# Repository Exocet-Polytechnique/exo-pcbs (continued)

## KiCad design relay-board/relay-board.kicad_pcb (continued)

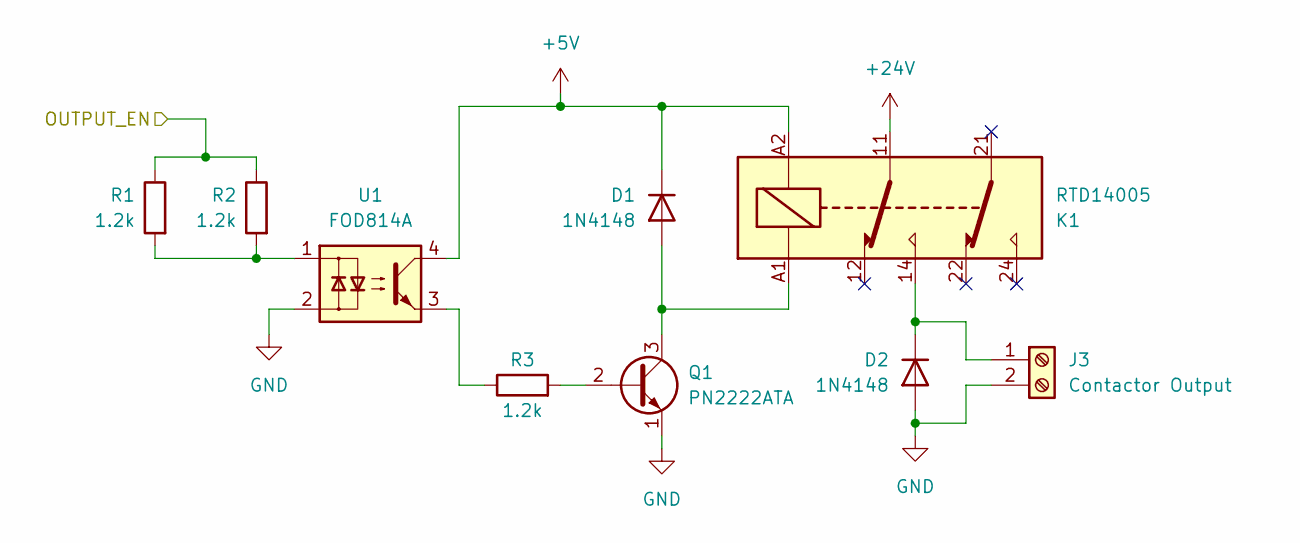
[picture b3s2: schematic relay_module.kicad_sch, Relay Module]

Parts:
D1, D2: 1N4148; D_DO-35_SOD27_P7.62mm_Horizontal
J3: Contactor Output; Wurth_Term_Blk_2pos_Side_Entry_5mm; MPN 691137710002
K1: RTD14005; Relay_DPDT_Schrack-RT2-FormC_RM5mm
Q1: PN2222ATA; TO-92_Inline
R1, R2, R3: 1.2k; R_Axial_DIN0207_L6.3mm_D2.5mm_P10.16mm_Horizontal
U1: FOD814A; DIP-4_W7.62mm

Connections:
+5V: D1.1 (K), K1.A2, U1.4; also elsewhere on the board
+24V: K1.11; also elsewhere on the board
/BOP_SWITCH: R1.1, R2.1; also elsewhere on the board
GND: D2.2 (A), J3.2, Q1.1 (E), U1.2; also elsewhere on the board
unnamed: D1.2 (A), K1.A1, Q1.3 (C)
unnamed: D2.1 (K), J3.1, K1.14
unnamed: Q1.2 (B), R3.2
unnamed: R1.2, R2.2, U1.1
unnamed: R3.1, U1.3

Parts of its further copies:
D3, D4, D5, D6, D7, D8, D9, D10, D11, D12, D13, D14, D15, D16: 1N4148; D_DO-35_SOD27_P7.62mm_Horizontal
J4, J5, J6, J7, J8, J9, J10: Contactor Output; Wurth_Term_Blk_2pos_Side_Entry_5mm; MPN 691137710002
K2, K3, K4, K5, K6, K7, K8: RTD14005; Relay_DPDT_Schrack-RT2-FormC_RM5mm
Q2, Q3, Q4, Q5, Q6, Q7, Q8: PN2222ATA; TO-92_Inline
R4, R5, R6, R7, R8, R9, R10, R11, R12, R13, R14, R15, R16, R17, R18, R19, R20, R21, R22, R23, R24: 1.2k; R_Axial_DIN0207_L6.3mm_D2.5mm_P10.16mm_Horizontal
U2, U3, U4, U5, U6, U7, U8: FOD814A; DIP-4_W7.62mm

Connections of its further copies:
+5V: D3.1 (K), D5.1 (K), D7.1 (K), D9.1 (K), D11.1 (K), D13.1 (K), D15.1 (K), K2.A2, K3.A2, K4.A2, K5.A2, K6.A2, K7.A2, K8.A2, U2.4, U3.4, U4.4, U5.4, U6.4, U7.4, U8.4; also elsewhere on the board
+24V: K2.11, K3.11, K4.11, K5.11, K6.11, K7.11, K8.11; also elsewhere on the board
/AUXILIARY_BATTERY_SWITCH: R22.1, R23.1; also elsewhere on the board
/BRAKING_RESISTOR: R19.1, R20.1; also elsewhere on the board
/MOTOR_PRECHARGE_STAGE_1: R13.1, R14.1; also elsewhere on the board
/MOTOR_PRECHARGE_STAGE_2: R16.1, R17.1; also elsewhere on the board
/MPPT_PRECHARGE_STAGE_1: R7.1, R8.1; also elsewhere on the board
/MPPT_PRECHARGE_STAGE_2: R10.1, R11.1; also elsewhere on the board
/STORAGE_BATTERY_SWITCH: R4.1, R5.1; also elsewhere on the board
GND: D4.2 (A), D6.2 (A), D8.2 (A), D10.2 (A), D12.2 (A), D14.2 (A), D16.2 (A), J4.2, J5.2, J6.2, J7.2, J8.2, J9.2, J10.2, Q2.1 (E), Q3.1 (E), Q4.1 (E), Q5.1 (E), Q6.1 (E), Q7.1 (E), Q8.1 (E), U2.2, U3.2, U4.2, U5.2, U6.2, U7.2, U8.2; also elsewhere on the board
unnamed: D3.2 (A), K2.A1, Q2.3 (C)
unnamed: D4.1 (K), J4.1, K2.14
unnamed: D5.2 (A), K3.A1, Q3.3 (C)
unnamed: D6.1 (K), J5.1, K3.14
unnamed: D7.2 (A), K4.A1, Q4.3 (C)
unnamed: D8.1 (K), J6.1, K4.14
unnamed: D9.2 (A), K5.A1, Q5.3 (C)
unnamed: D10.1 (K), J7.1, K5.14
unnamed: D11.2 (A), K6.A1, Q6.3 (C)
unnamed: D12.1 (K), J8.1, K6.14
unnamed: D13.2 (A), K7.A1, Q7.3 (C)
unnamed: D14.1 (K), J9.1, K7.14
unnamed: D15.2 (A), K8.A1, Q8.3 (C)
unnamed: D16.1 (K), J10.1, K8.14
unnamed: Q2.2 (B), R6.2
unnamed: Q3.2 (B), R9.2
unnamed: Q4.2 (B), R12.2
unnamed: Q5.2 (B), R15.2
unnamed: Q6.2 (B), R18.2
unnamed: Q7.2 (B), R21.2
unnamed: Q8.2 (B), R24.2
unnamed: R4.2, R5.2, U2.1
unnamed: R6.1, U2.3
unnamed: R7.2, R8.2, U3.1
unnamed: R9.1, U3.3
unnamed: R10.2, R11.2, U4.1
unnamed: R12.1, U4.3
unnamed: R13.2, R14.2, U5.1
unnamed: R15.1, U5.3
unnamed: R16.2, R17.2, U6.1
unnamed: R18.1, U6.3
unnamed: R19.2, R20.2, U7.1
unnamed: R21.1, U7.3
unnamed: R22.2, R23.2, U8.1
unnamed: R24.1, U8.3

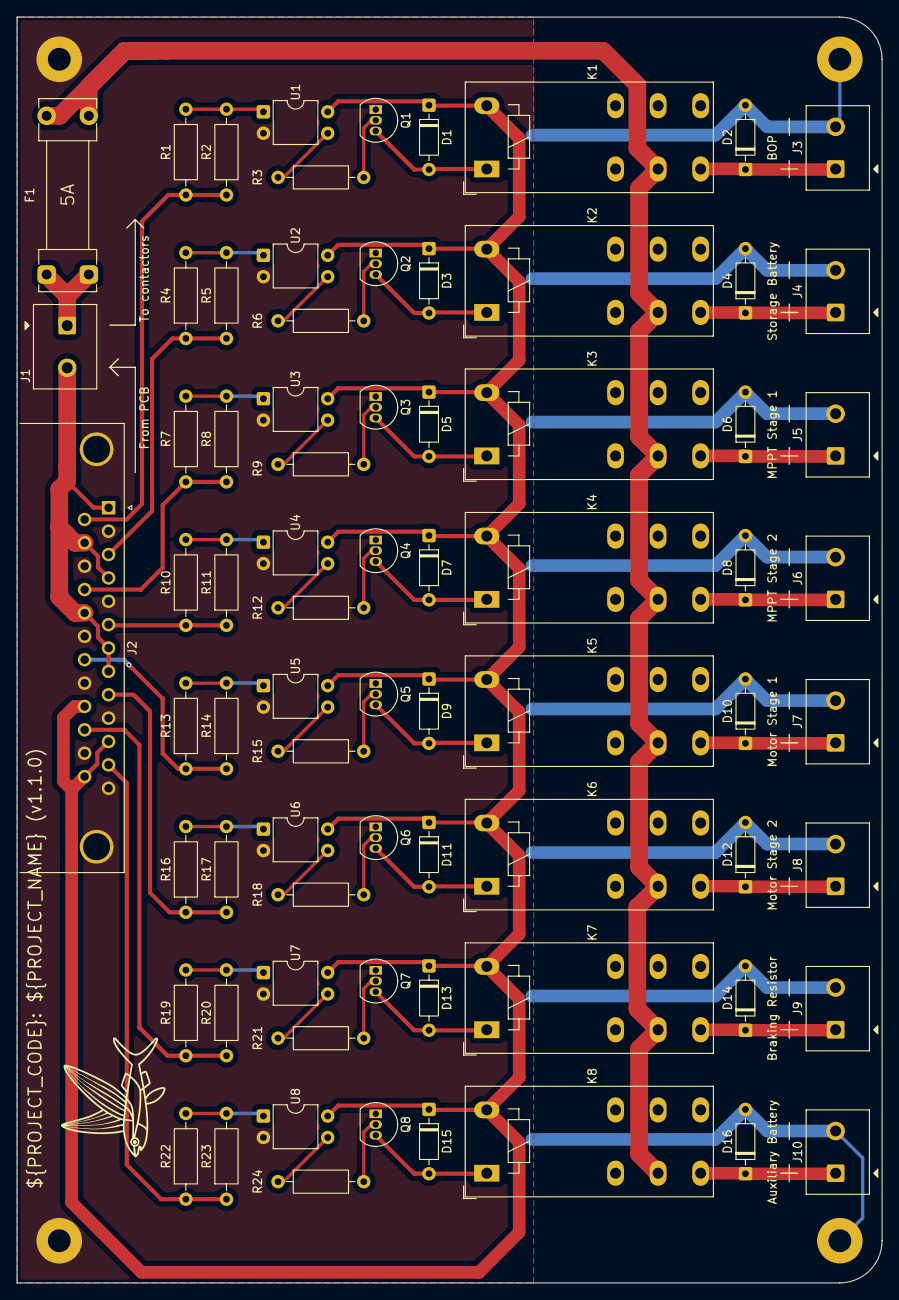
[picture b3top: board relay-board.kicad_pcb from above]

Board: 2 copper layers, 102.5 x 150.0 mm, 79 parts (0 on the bottom side), 53 nets.

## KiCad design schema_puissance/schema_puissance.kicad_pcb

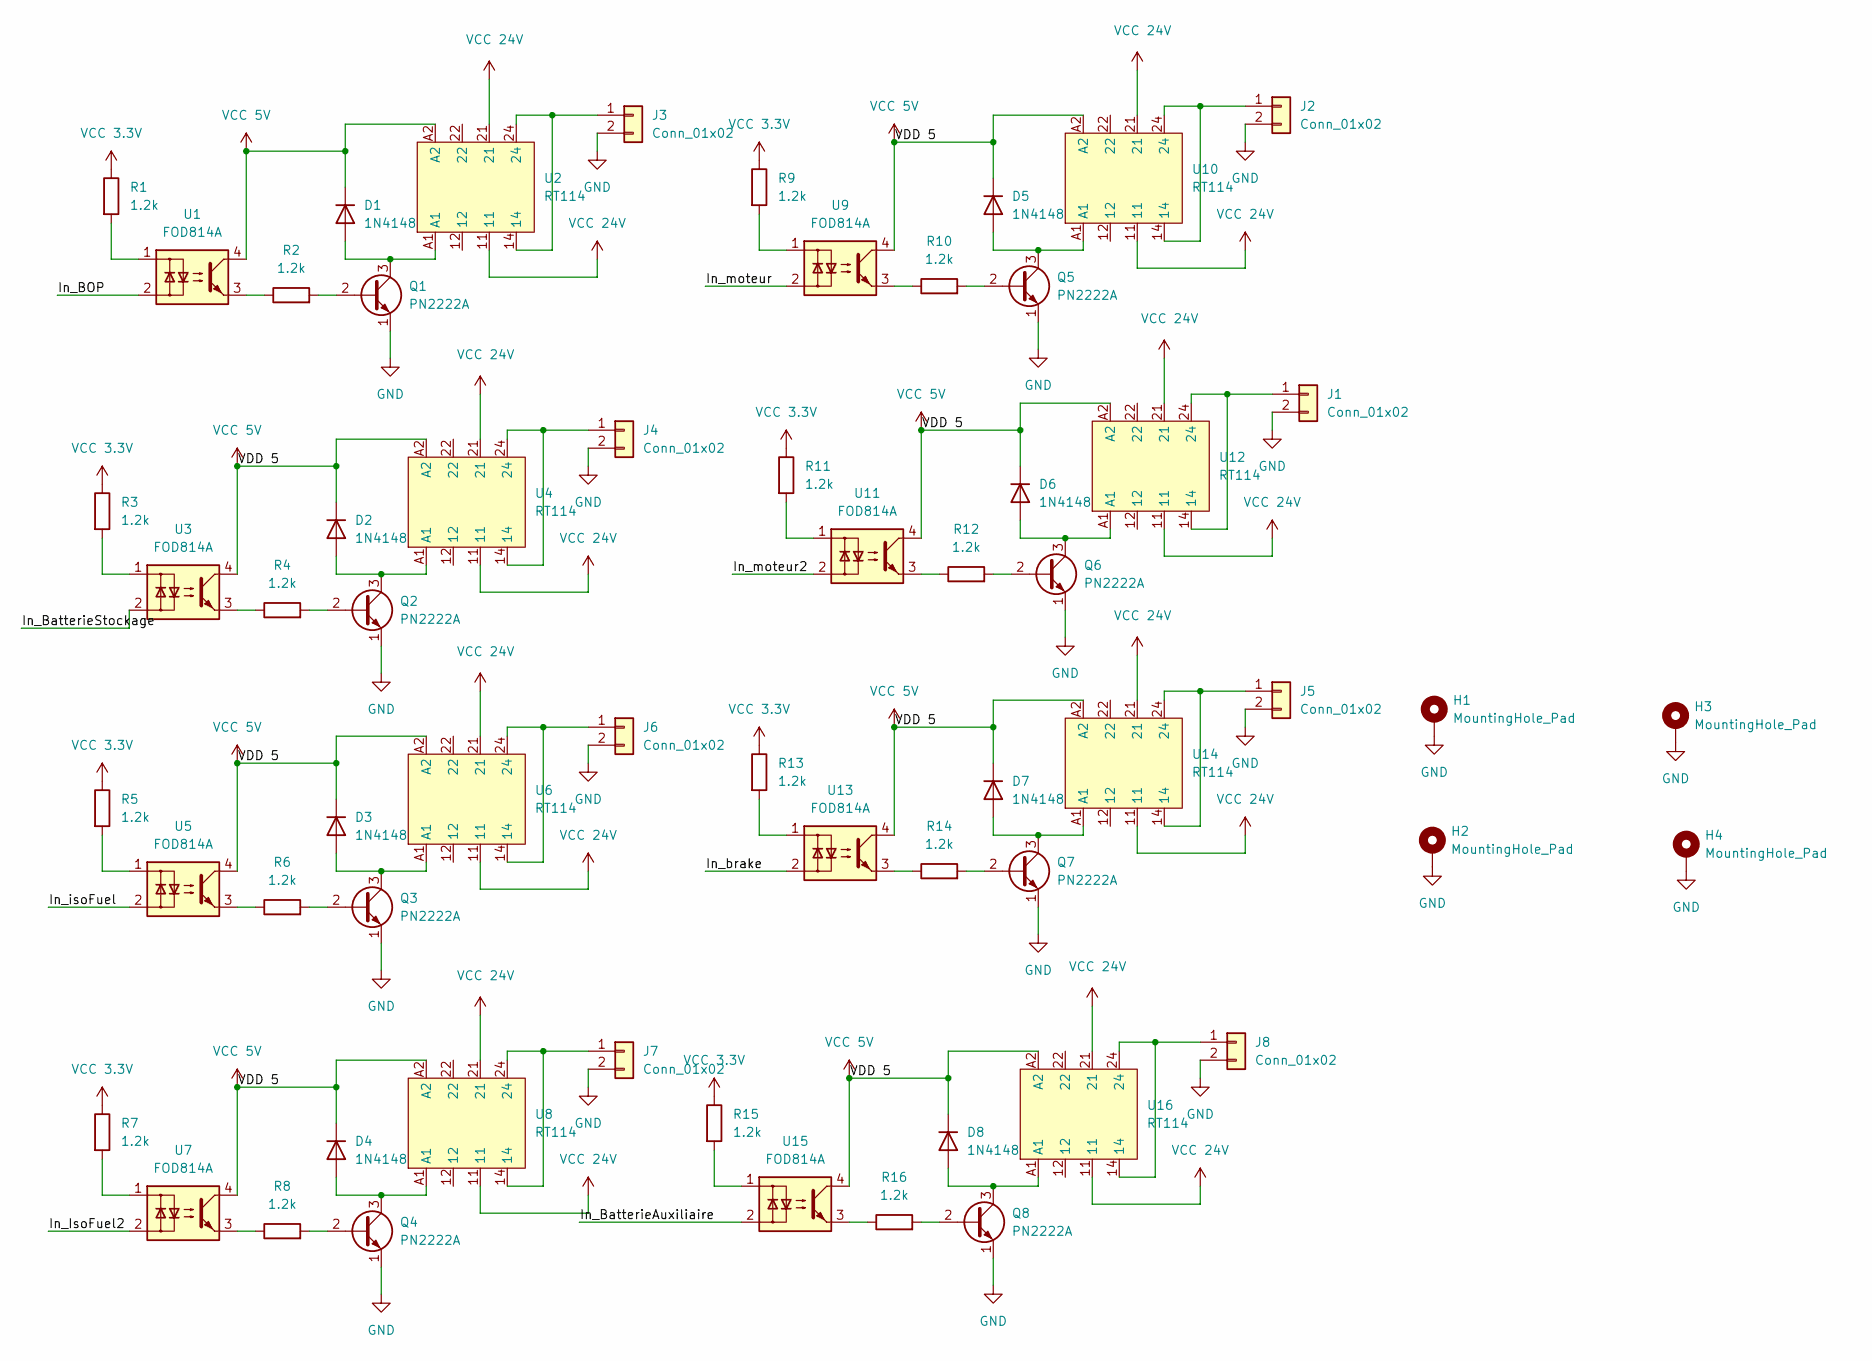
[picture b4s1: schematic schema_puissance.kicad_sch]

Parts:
D1, D2, D3, D4, D5, D6, D7, D8: 1N4148; D_DO-35_SOD27_P7.62mm_Horizontal
H1, H2, H3, H4: MountingHole_Pad; MountingHole_2.7mm_Pad
J1, J2, J3, J4, J5, J6, J7, J8: Conn_01x02; TerminalBlock_MaiXu_MX126-5.0-02P_1x02_P5.00mm
Q1, Q2, Q3, Q4, Q5, Q6, Q7, Q8: PN2222A; TO-92_Inline
R1, R2, R3, R4, R5, R6, R7, R8, R9, R10, R11, R12, R13, R14, R15, R16: 1.2k; R_Axial_DIN0309_L9.0mm_D3.2mm_P12.70mm_Horizontal
U1, U3, U5, U7, U9, U11, U13, U15: FOD814A; DIP-4_W7.62mm
U2, U4, U6, U8, U10, U12, U14, U16: RT114; Relay_DPDT_Schrack-RT2-FormC_RM5mm

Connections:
/In_BOP: U1.2
/In_BatterieAuxiliaire: U15.2
/In_BatterieStockage: U3.2
/In_IsoFuel2: U7.2
/In_brake: U13.2
/In_isoFuel: U5.2
/In_moteur: U9.2
/In_moteur2: U11.2
GND: H1.1, H2.1, H3.1, H4.1, J1.2, J2.2, J3.2, J4.2, J5.2, J6.2, J7.2, J8.2, Q1.1 (E), Q2.1 (E), Q3.1 (E), Q4.1 (E), Q5.1 (E), Q6.1 (E), Q7.1 (E), Q8.1 (E)
unnamed: D1.2 (A), Q1.3 (C), U2.A1
unnamed: D2.2 (A), Q2.3 (C), U4.A1
unnamed: D3.2 (A), Q3.3 (C), U6.A1
unnamed: D4.2 (A), Q4.3 (C), U8.A1
unnamed: D5.2 (A), Q5.3 (C), U10.A1
unnamed: D6.2 (A), Q6.3 (C), U12.A1
unnamed: D7.2 (A), Q7.3 (C), U14.A1
unnamed: D8.2 (A), Q8.3 (C), U16.A1
unnamed: J1.1, U12.14, U12.24
unnamed: J2.1, U10.14, U10.24
unnamed: J3.1, U2.14, U2.24
unnamed: J4.1, U4.14, U4.24
unnamed: J5.1, U14.14, U14.24
unnamed: J6.1, U6.14, U6.24
unnamed: J7.1, U8.14, U8.24
unnamed: J8.1, U16.14, U16.24
unnamed: Q1.2 (B), R2.2
unnamed: Q2.2 (B), R4.2
unnamed: Q3.2 (B), R6.2
unnamed: Q4.2 (B), R8.2
unnamed: Q5.2 (B), R10.2
unnamed: Q6.2 (B), R12.2
unnamed: Q7.2 (B), R14.2
unnamed: Q8.2 (B), R16.2
unnamed: R1.2, U1.1
unnamed: R2.1, U1.3
unnamed: R3.2, U3.1
unnamed: R4.1, U3.3
unnamed: R5.2, U5.1
unnamed: R6.1, U5.3
unnamed: R7.2, U7.1
unnamed: R8.1, U7.3
unnamed: R9.2, U9.1
unnamed: R10.1, U9.3
unnamed: R11.2, U11.1
unnamed: R12.1, U11.3
unnamed: R13.2, U13.1
unnamed: R14.1, U13.3
unnamed: R15.2, U15.1
unnamed: R16.1, U15.3
VCC 3.3V: R1.1, R3.1, R5.1, R7.1, R9.1, R11.1, R13.1, R15.1
VCC 5V: D1.1 (K), D2.1 (K), D3.1 (K), D4.1 (K), D5.1 (K), D6.1 (K), D7.1 (K), D8.1 (K), U1.4, U2.A2, U3.4, U4.A2, U5.4, U6.A2, U7.4, U8.A2, U9.4, U10.A2, U11.4, U12.A2, U13.4, U14.A2, U15.4, U16.A2
VCC 24V: U2.11, U2.21, U4.11, U4.21, U6.11, U6.21, U8.11, U8.21, U10.11, U10.21, U12.11, U12.21, U14.11, U14.21, U16.11, U16.21

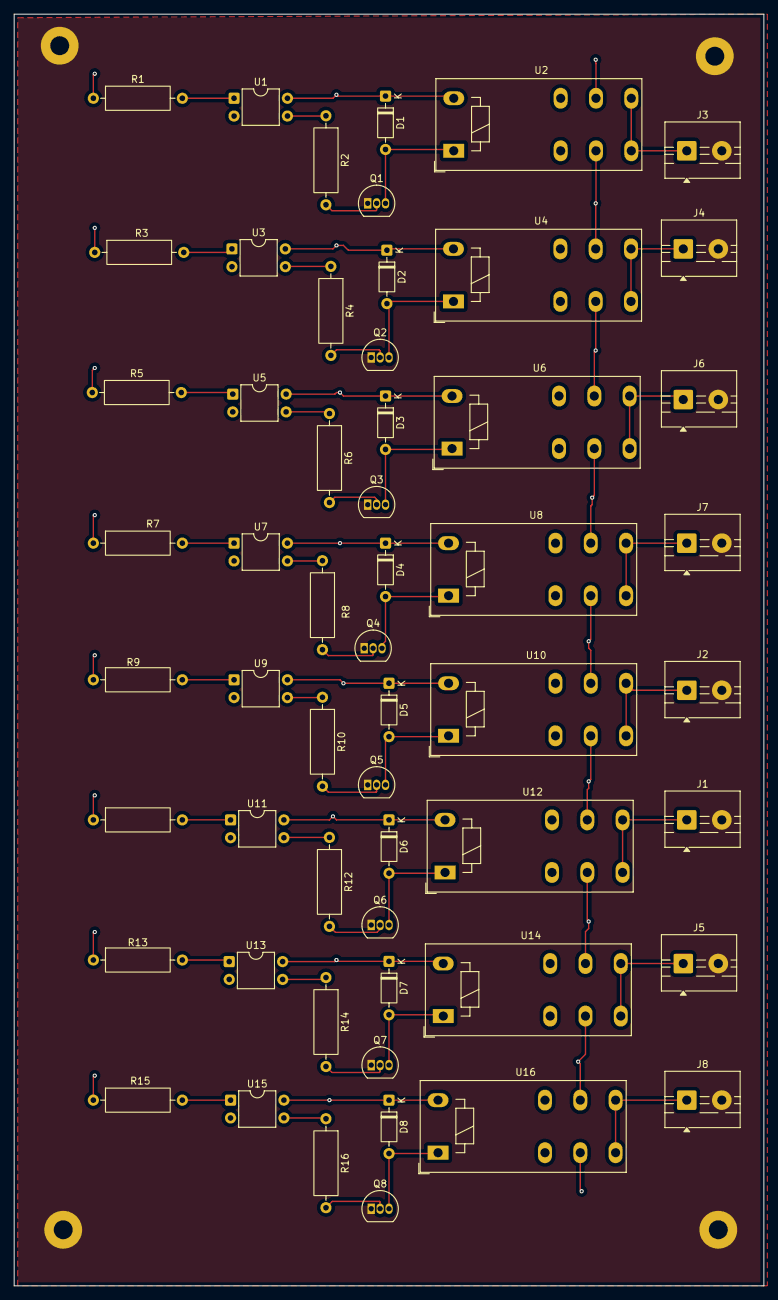
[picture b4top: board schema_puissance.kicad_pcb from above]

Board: 2 copper layers, 107.0 x 181.5 mm, 60 parts (0 on the bottom side), 44 nets.

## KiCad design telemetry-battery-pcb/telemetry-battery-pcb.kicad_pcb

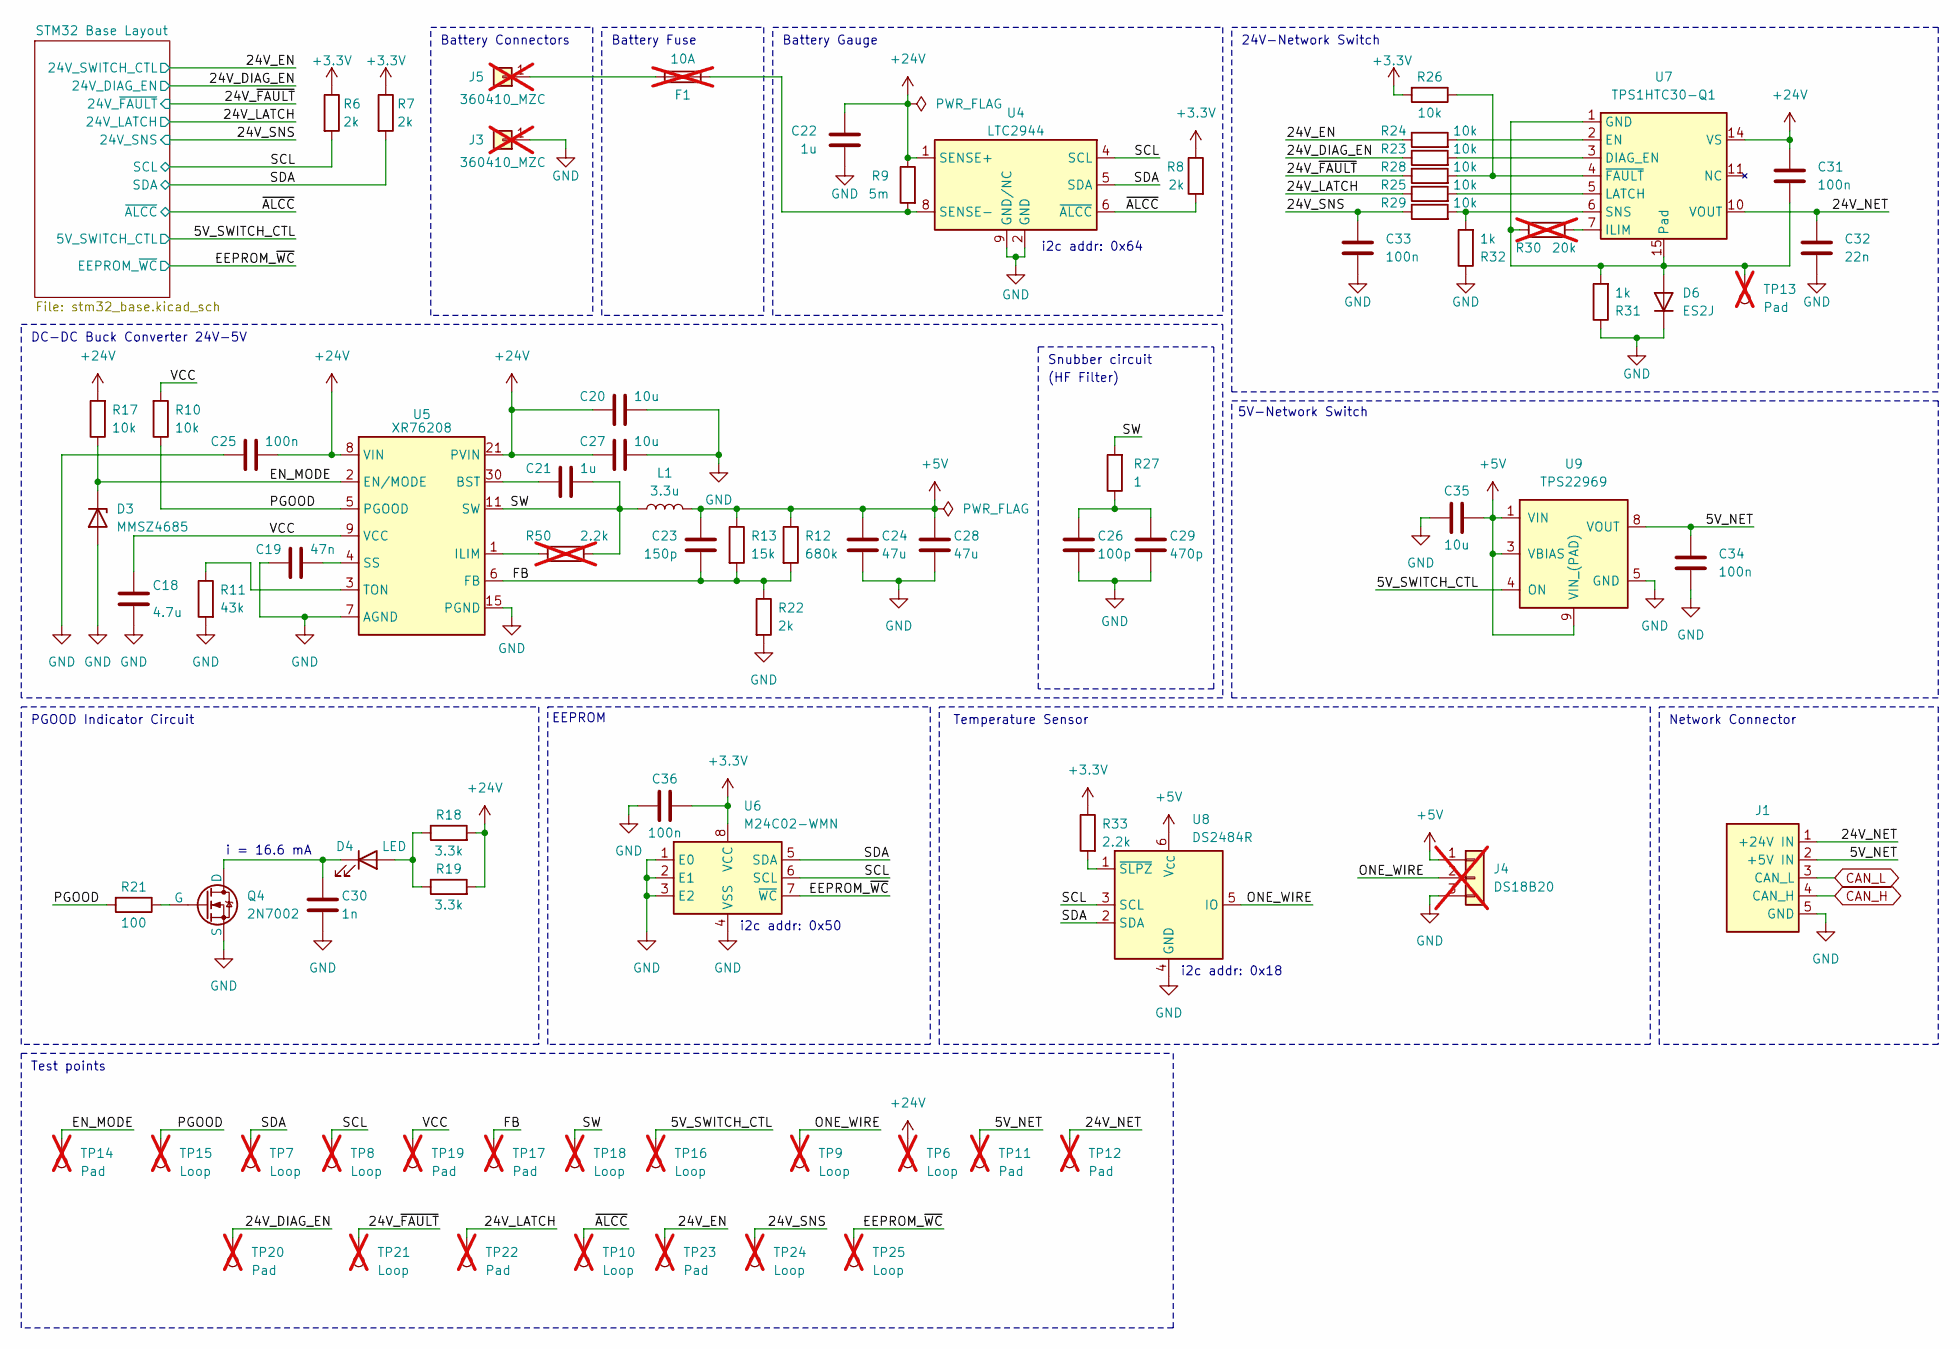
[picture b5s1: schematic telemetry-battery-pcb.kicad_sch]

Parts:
C18: 4.7u; C_0402_1005Metric; JLCPCB C23733
C19: 47n; C_0603_1608Metric; JLCPCB C1622
C20, C27: 10u; C_1206_3216Metric; JLCPCB C13585
C21, C22: 1u; C_0603_1608Metric; JLCPCB C15849
C23: 150p; C_0603_1608Metric; JLCPCB C1594
C24, C28: 47u; C_1206_3216Metric; JLCPCB C96123
C25, C31: 100n; C_0603_1608Metric; JLCPCB C14663
C26: 100p; C_0402_1005Metric; JLCPCB C1546
C29: 470p; C_0603_1608Metric; JLCPCB C1620
C30: 1n; C_0402_1005Metric; JLCPCB C1523
C32: 22n; C_0603_1608Metric; JLCPCB C21122
C33, C34, C36: 100n; C_0402_1005Metric; JLCPCB C1525
C35: 10u; C_0603_1608Metric; JLCPCB C96446
D3: MMSZ4685; D_SOD-123; JLCPCB C22395546
D4: LED; LED_0603_1608Metric; JLCPCB C2286
D6: ES2J; D_SMA; JLCPCB C7420341
F1: 10A; Fuseholder_Littelfuse_Combined; not fitted
J1: Network Connector; Molex_SPOX_5268-05A_1x05_P2.50mm_Horizontal; JLCPCB C185201
J3, J5: 360410_MZC; CONN_360410_MZC; not fitted
J4: DS18B20; JST_PH_S3B-PH-K_1x03_P2.00mm_Horizontal; not fitted
L1: 3.3u; L_Sunlord_MWSA1005S; JLCPCB C167229
Q4: 2N7002; SOT-23; JLCPCB C8545
R6, R7, R8, R22: 2k; R_0402_1005Metric; JLCPCB C4109
R9: 5m; R_2512_6332Metric; JLCPCB C185817
R10, R17, R23, R24, R25, R26, R28, R29: 10k; R_0402_1005Metric; JLCPCB C25744
R11: 43k; R_0603_1608Metric; JLCPCB C23172
R12: 680k; R_0805_2012Metric; JLCPCB C17797
R13: 15k; R_0603_1608Metric; JLCPCB C22809
R18, R19: 3.3k; R_0805_2012Metric; JLCPCB C26010
R21: 100; R_1206_3216Metric; JLCPCB C17901
R27: 1; R_0603_1608Metric; JLCPCB C22936
R30: 20k; R_Axial_DIN0309_L9.0mm_D3.2mm_P12.70mm_Horizontal; not fitted
R31, R32: 1k; R_0402_1005Metric; JLCPCB C11702
R33: 2.2k; R_0603_1608Metric; JLCPCB C4190
R50: 2.2k; R_Axial_DIN0309_L9.0mm_D3.2mm_P12.70mm_Horizontal; not fitted
TP6, TP7, TP8, TP9, TP10, TP15, TP16, TP18, TP21, TP24, TP25: Loop; TestPoint_Keystone_5005-5009_Compact; not fitted
TP11, TP12, TP13, TP14, TP17, TP19, TP20, TP22, TP23: Pad; TestPoint_Pad_D2.0mm; not fitted
U4: LTC2944; DFN-8-1EP_3x3mm_P0.5mm_EP1.66x2.38mm; JLCPCB C683670
U5: XR76208; MaxLinear_XR76208ELTR-F_QFN-30(5x5); JLCPCB C1355299
U6: M24C02-WMN; SOIC-8_3.9x4.9mm_P1.27mm; JLCPCB C7562
U7: TPS1HTC30-Q1; Tps1htc_Exocet_Texas_HTSSOP-14-1EP_4.4x5mm_P0.65mm_EP3.4x5m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; JLCPCB C22414694
U8: DS2484R; SOT-23-6; JLCPCB C124886
U9: TPS22969; TPS22969_WSON-8_3x3mm_Thermal_Pad; JLCPCB C2867191

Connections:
+3.3V: C36.2, R6.1, R7.1, R8.1, R26.2, R33.1, U6.8 (VCC); also elsewhere on the board
+5V: C23.1, C24.1, C28.1, C35.2, J4.1, L1.2, R12.1, R13.1, U8.6 (V_{CC}), U9.1 (VIN), U9.2 (VIN), U9.3 (VBIAS), U9.9 (VIN_(PAD)); also elsewhere on the board
+24V: C20.1, C22.1, C25.1, C27.1, C31.1, R9.1, R17.2, R18.2, R19.2, TP6.1, U4.1 (SENSE+), U5.8 (VIN), U5.21 (PVIN), U7.12 (VS), U7.13 (VS), U7.14 (VS)
/5V_NET: C34.1, J1.2 (+5V IN), TP11.1, U9.6 (VOUT), U9.7 (VOUT), U9.8 (VOUT)
/5V_SWITCH_CTL: TP16.1, U9.4 (ON); also elsewhere on the board
/24V_DIAG_EN: R23.1, TP20.1; also elsewhere on the board
/24V_EN: R24.1, TP23.1; also elsewhere on the board
/24V_LATCH: R25.1, TP22.1; also elsewhere on the board
/24V_NET: C32.1, J1.1 (+24V IN), TP12.1, U7.8 (VOUT), U7.9 (VOUT), U7.10 (VOUT)
/24V_SNS: C33.1, R29.1, TP24.1; also elsewhere on the board
/24V_~FAULT: R28.1, TP21.1; also elsewhere on the board
/EEPROM_~WC: TP25.1, U6.7 (~WC); also elsewhere on the board
/EN_MODE: D3.1 (K), R17.1, TP14.1, U5.2 (EN/MODE)
/FB: C23.2, R12.2, R13.2, R22.1, TP17.1, U5.6 (FB)
/ONE_WIRE: J4.2, TP9.1, U8.5 (IO)
/PGOOD: R10.1, R21.2, TP15.1, U5.5 (PGOOD)
/SCL: R6.2, TP8.1, U4.4 (SCL), U6.6 (SCL), U8.3 (SCL); also elsewhere on the board
/SDA: R7.2, TP7.1, U4.5 (SDA), U6.5 (SDA), U8.2 (SDA); also elsewhere on the board
/SW: C21.1, L1.1, R27.2, R50.1, TP18.1, U5.11 (SW)
/VCC: C18.1, R10.2, TP19.1, U5.9 (VCC)
/~ALCC: R8.2, TP10.1, U4.6 (~ALCC); also elsewhere on the board
CAN_H: J1.4 (CAN_H); also elsewhere on the board
CAN_L: J1.3 (CAN_L); also elsewhere on the board
GND: C18.2, C19.2, C20.2, C22.2, C24.2, C25.2, C26.1, C27.2, C28.2, C29.1, C30.2, C32.2, C33.2, C34.2, C35.1, C36.1, D3.2 (A), D6.1 (K), J1.5 (GND), J3.1, J3.2, J4.3, Q4.3 (S), R11.2, R22.2, R31.1, R32.1, U4.2 (GND), U4.3 (GND), U4.7 (GND), U4.9 (GND/NC), U5.7 (AGND), U5.15 (PGND), U6.1 (E0), U6.2 (E1), U6.3 (E2), U6.4 (VSS), U8.4 (GND), U9.5 (GND); also elsewhere on the board
unnamed: C26.2, C29.2, R27.1
unnamed: D4.2 (A), R18.1, R19.1
unnamed: C30.1, D4.1 (K), Q4.1 (D)
unnamed: C31.2, D6.2 (A), R30.1, R31.2, TP13.1, U7.1 (GND), U7.15 (Pad)
unnamed: F1.1, J5.1, J5.2
unnamed: Q4.2 (G), R21.1
unnamed: F1.2, R9.2, U4.8 (SENSE-)
unnamed: C21.2, U5.30 (BST)
unnamed: R50.2, U5.1 (ILIM)
unnamed: C19.1, U5.4 (SS)
unnamed: R11.1, U5.3 (TON)
unnamed: R23.2, U7.3 (DIAG_EN)
unnamed: R24.2, U7.2 (EN)
unnamed: R30.2, U7.7 (ILIM)
unnamed: R25.2, U7.5 (LATCH)
unnamed: R29.2, R32.2, U7.6 (SNS)
unnamed: R26.1, R28.2, U7.4 (~FAULT)
unnamed: R33.2, U8.1 (~SLPZ)

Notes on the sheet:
Network Connector
Temperature Sensor
i2c addr: 0x50
Battery Gauge
i = 16.6 mA
(HF Filter)
Battery Connectors
24V-Network Switch
EEPROM
PGOOD Indicator Circuit
Snubber circuit
Test points
5V-Network Switch
i2c addr: 0x64
DC-DC Buck Converter 24V-5V
i2c addr: 0x18
Battery Fuse

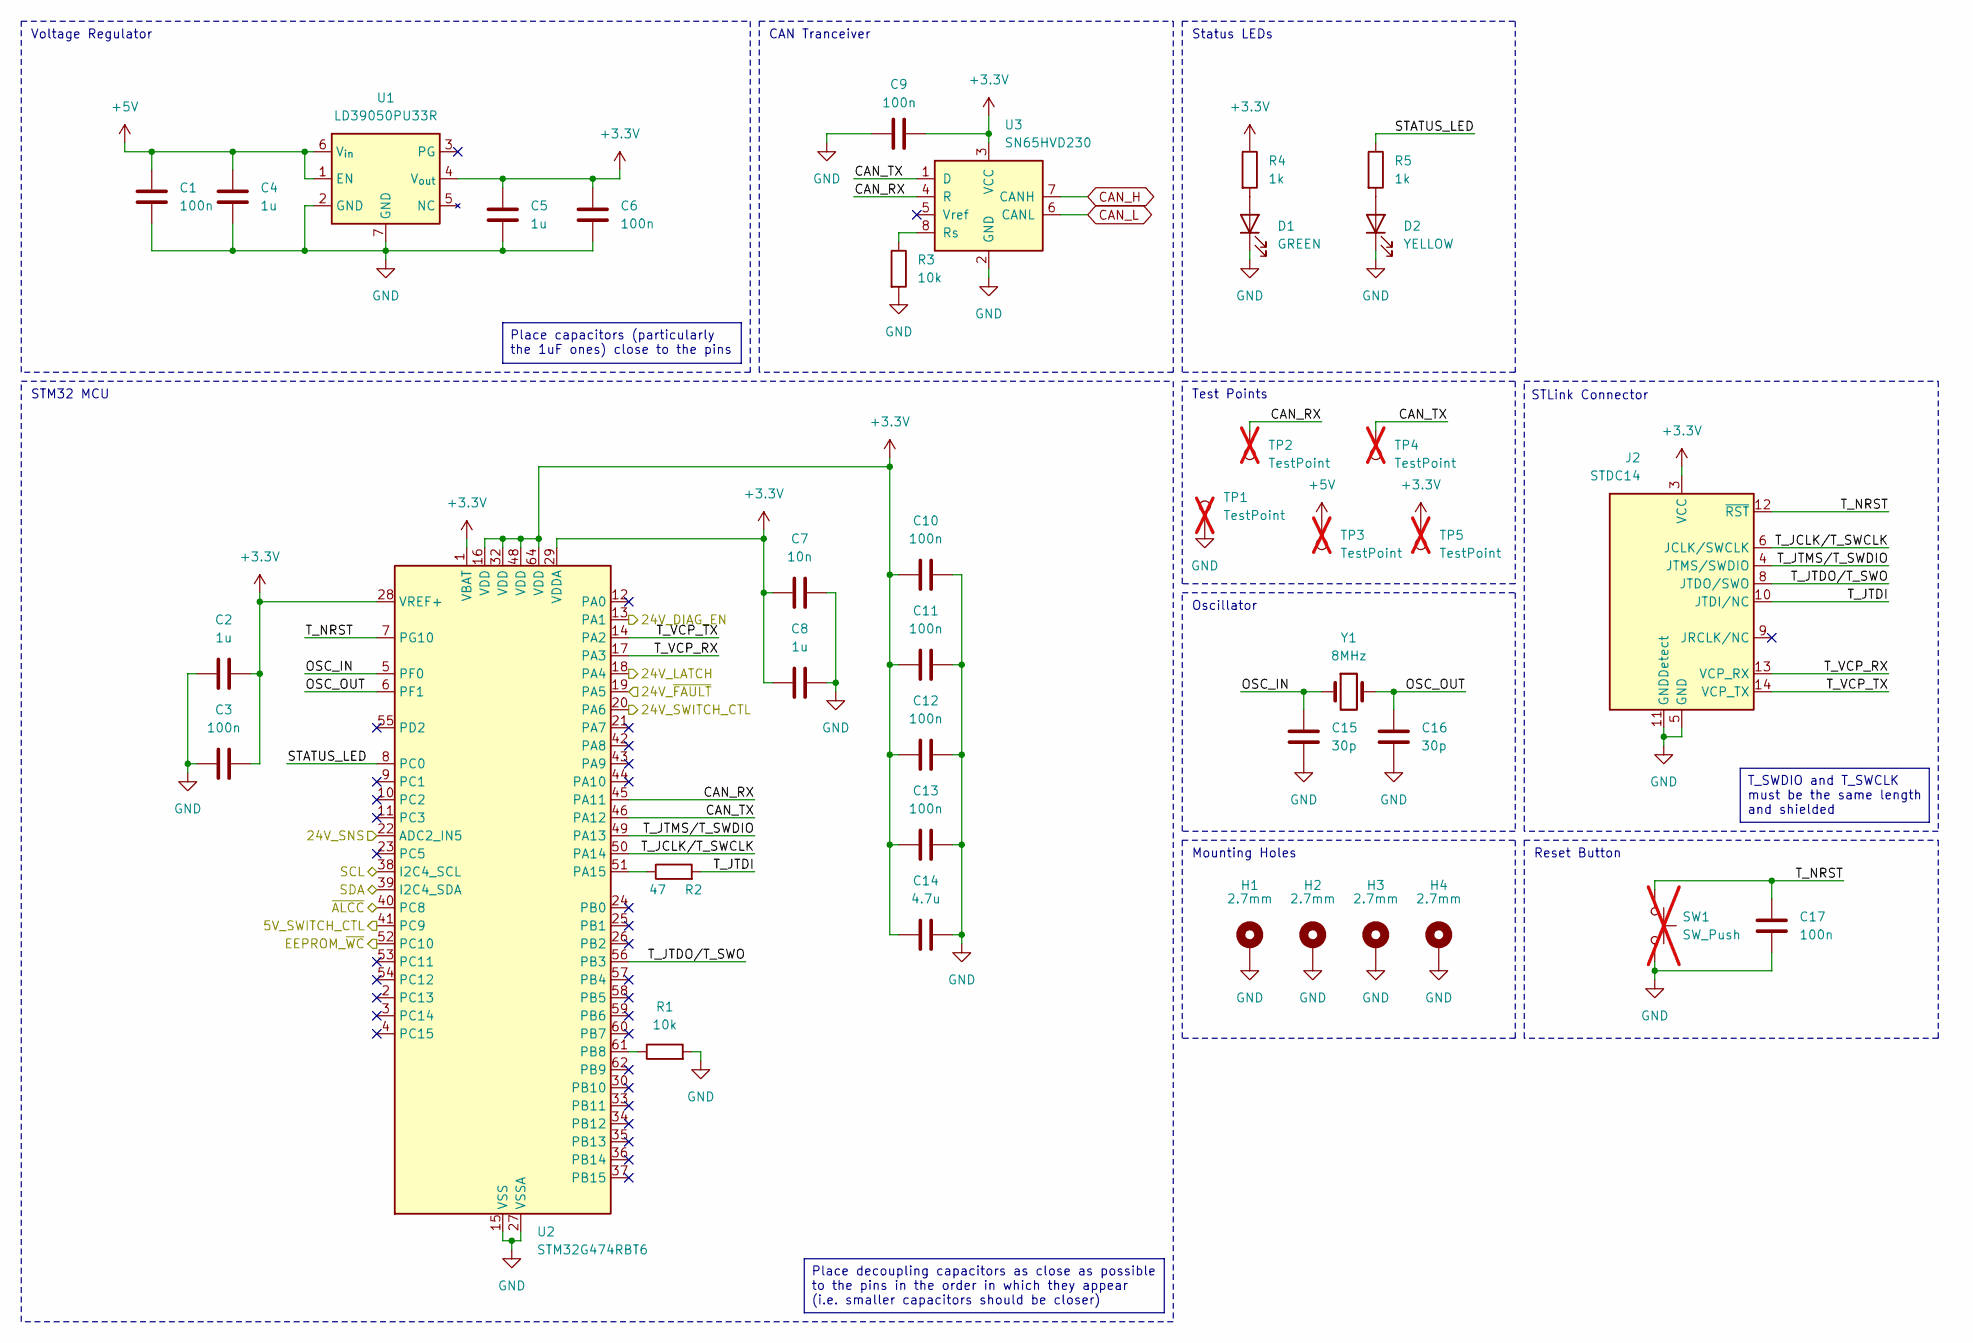
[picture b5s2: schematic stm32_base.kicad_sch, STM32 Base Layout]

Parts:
C1, C3, C6, C9, C10, C11, C12, C13, C17: 100n; C_0402_1005Metric; JLCPCB C1525
C2, C4, C5, C8: 1u; C_0402_1005Metric; JLCPCB C52923
C7: 10n; C_0402_1005Metric; JLCPCB C15195
C14: 4.7u; C_0402_1005Metric; JLCPCB C23733
C15, C16: 30p; C_0603_1608Metric; JLCPCB C1658
D1: GREEN; LED_0805_2012Metric_With_Annotations; JLCPCB C2297
D2: YELLOW; LED_0805_2012Metric_With_Annotations; JLCPCB C2296
H1, H2, H3, H4: 2.7mm; MountingHole_2.7mm_Pad
J2: STDC14; PinHeader_2x07_P1.27mm_Vertical_SMD; JLCPCB C7465995
R1, R3: 10k; R_0402_1005Metric; JLCPCB C25744
R2: 47; R_0603_1608Metric; JLCPCB C23182
R4, R5: 1k; R_0402_1005Metric; JLCPCB C11702
SW1: SW_Push; SW_PUSH_6mm; not fitted
TP1, TP2, TP3, TP4, TP5: TestPoint; TestPoint_Keystone_5005-5009_Compact; not fitted
U1: LD39050PU33R; DFN-6-1EP_3x3mm_P0.95mm_EP1.7x2.6mm; JLCPCB C132827
U2: STM32G474RBT6; LQFP-64_10x10mm_P0.5mm; JLCPCB C529413
U3: SN65HVD230; SOIC-8_3.9x4.9mm_P1.27mm; JLCPCB C12084
Y1: 8MHz; Crystal_SMD_HC49-SD; Part Name X49SM8MSD2SC; JLCPCB C12674

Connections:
+3.3V: C2.2, C3.2, C5.1, C6.1, C7.1, C8.1, C9.1, C10.1, C11.1, C12.1, C13.1, C14.1, J2.3 (VCC), R4.1, TP5.1, U1.4 (V_{out}), U2.1 (VBAT), U2.16 (VDD), U2.28 (VREF+), U2.29 (VDDA), U2.32 (VDD), U2.48 (VDD), U2.64 (VDD), U3.3 (VCC); also elsewhere on the board
+5V: C1.1, C4.1, TP3.1, U1.1 (EN), U1.6 (V_{in}); also elsewhere on the board
/5V_SWITCH_CTL: U2.41 (PC9); also elsewhere on the board
/24V_DIAG_EN: U2.13 (PA1); also elsewhere on the board
/24V_EN: U2.20 (PA6); also elsewhere on the board
/24V_LATCH: U2.18 (PA4); also elsewhere on the board
/24V_SNS: U2.22 (ADC2_IN5); also elsewhere on the board
/24V_~FAULT: U2.19 (PA5); also elsewhere on the board
/EEPROM_~WC: U2.52 (PC10); also elsewhere on the board
/SCL: U2.38 (I2C4_SCL); also elsewhere on the board
/SDA: U2.39 (I2C4_SDA); also elsewhere on the board
/STM32 Base Layout/CAN_RX: TP2.1, U2.45 (PA11), U3.4 (R)
/STM32 Base Layout/CAN_TX: TP4.1, U2.46 (PA12), U3.1 (D)
/STM32 Base Layout/OSC_IN: C15.1, U2.5 (PF0), Y1.1
/STM32 Base Layout/OSC_OUT: C16.1, U2.6 (PF1), Y1.2
/STM32 Base Layout/STATUS_LED: R5.1, U2.8 (PC0)
/STM32 Base Layout/T_JCLK/T_SWCLK: J2.6 (JCLK/SWCLK), U2.50 (PA14)
/STM32 Base Layout/T_JTDI: J2.10 (JTDI/NC), R2.2
/STM32 Base Layout/T_JTDO/T_SWO: J2.8 (JTDO/SWO), U2.56 (PB3)
/STM32 Base Layout/T_JTMS/T_SWDIO: J2.4 (JTMS/SWDIO), U2.49 (PA13)
/STM32 Base Layout/T_NRST: C17.2, J2.12 (~RST), SW1.1, U2.7 (PG10)
/STM32 Base Layout/T_VCP_RX: J2.13 (VCP_RX), U2.17 (PA3)
/STM32 Base Layout/T_VCP_TX: J2.14 (VCP_TX), U2.14 (PA2)
/~ALCC: U2.40 (PC8); also elsewhere on the board
CAN_H: U3.7 (CANH); also elsewhere on the board
CAN_L: U3.6 (CANL); also elsewhere on the board
GND: C1.2, C2.1, C3.1, C4.2, C5.2, C6.2, C7.2, C8.2, C9.2, C10.2, C11.2, C12.2, C13.2, C14.2, C15.2, C16.2, C17.1, D1.1 (K), D2.1 (K), H1.1, H2.1, H3.1, H4.1, J2.5 (GND), J2.7 (GND), J2.11 (GNDDetect), R1.2, R3.2, SW1.2, TP1.1, U1.2 (GND), U1.7 (GND), U2.15 (VSS), U2.27 (VSSA), U2.31 (VSS), U2.47 (VSS), U2.63 (VSS), U3.2 (GND); also elsewhere on the board
unnamed: D1.2 (A), R4.2
unnamed: D2.2 (A), R5.2
unnamed: R2.1, U2.51 (PA15)
unnamed: R1.1, U2.61 (PB8)
unnamed: R3.1, U3.8 (Rs)

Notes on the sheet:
Oscillator
Reset Button
Mounting Holes
Voltage Regulator
CAN Tranceiver
Status LEDs
STLink Connector
Test Points
STM32 MCU
T_SWDIO and T_SWCLK must be the same length and shielded
Place capacitors (particularly the 1uF ones) close to the pins
Place decoupling capacitors as close as possible to the pins in the order in which they appear (i.e. smaller capacitors should be closer)

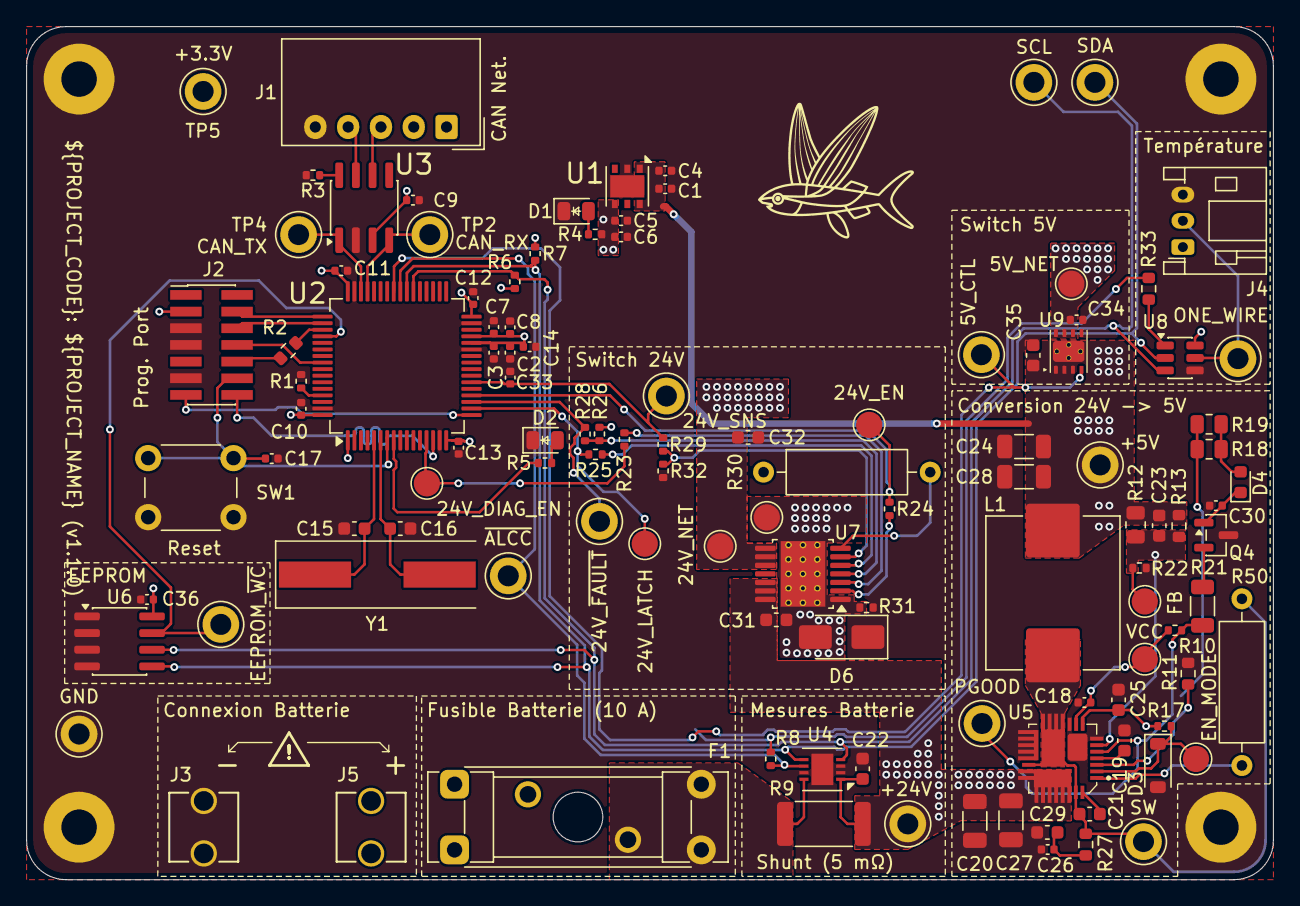
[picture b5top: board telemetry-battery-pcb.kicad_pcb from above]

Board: 2 copper layers, 95.0 x 65.0 mm, 119 parts (0 on the bottom side), 59 nets.

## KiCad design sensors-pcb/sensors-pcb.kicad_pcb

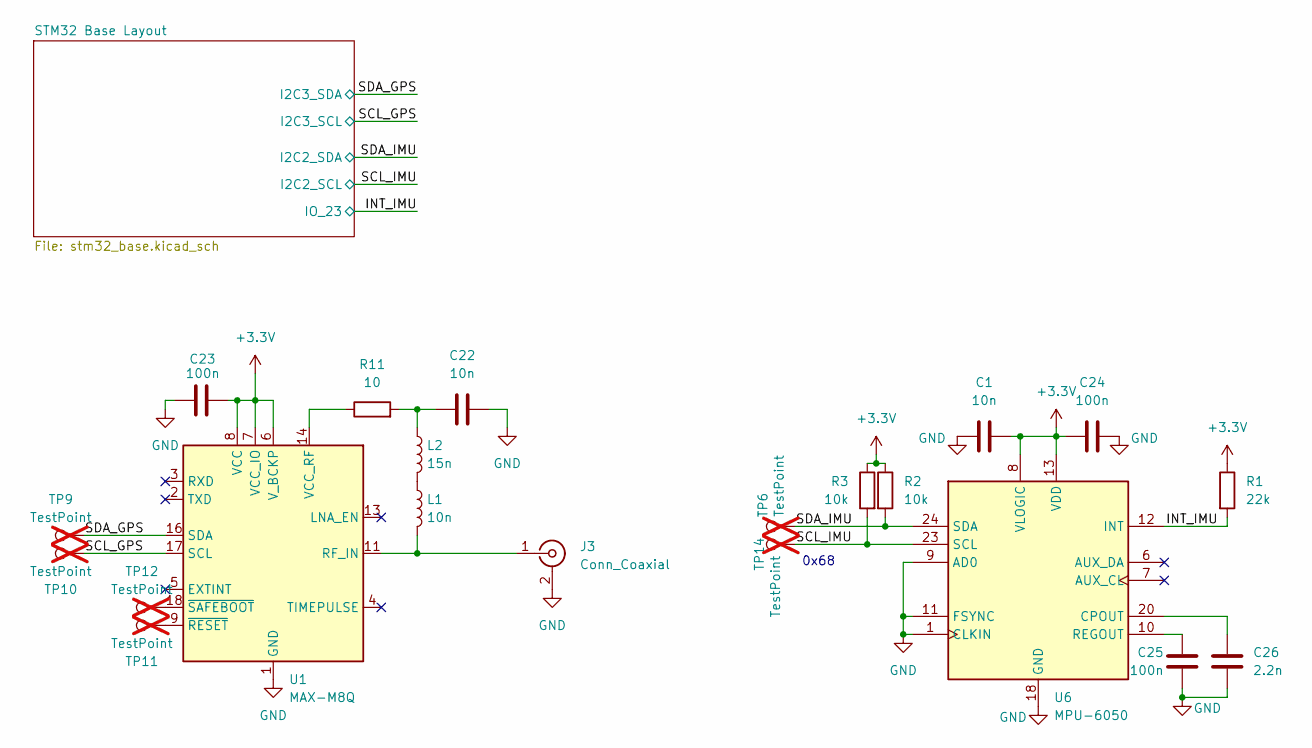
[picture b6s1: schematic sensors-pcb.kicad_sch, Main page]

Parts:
C1, C22: 10n; C_0402_1005Metric; JLCPCB C15195
C23, C24, C25: 100n; C_0402_1005Metric; JLCPCB C1525
C26: 2.2n; C_0402_1005Metric; JLCPCB C1531
J3: Conn_Coaxial; ANT-SMD_KH-IPEX-K501-29; JLCPCB C411563
L1: 10n; L_0402_1005Metric; JLCPCB C27147
L2: 15n; L_0402_1005Metric; JLCPCB C27143
R1: 22k; R_0402_1005Metric; JLCPCB C25768
R2, R3: 10k; R_0402_1005Metric; JLCPCB C25744
R11: 10; R_0402_1005Metric; JLCPCB C25077
TP6, TP9, TP10, TP11, TP12, TP14: TestPoint; TestPoint_Keystone_5005-5009_Compact; not fitted
U1: MAX-M8Q; ublox_MAX; JLCPCB C6898733
U6: MPU-6050; InvenSense_QFN-24_4x4mm_P0.5mm; JLCPCB C24112

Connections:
+3.3V: C1.2, C23.2, C24.1, R1.1, R2.1, R3.1, U1.6 (V_BCKP), U1.7 (VCC_IO), U1.8 (VCC), U6.8 (VLOGIC), U6.13 (VDD); also elsewhere on the board
/INT_IMU: R1.2, U6.12 (INT); also elsewhere on the board
/SCL_GPS: TP10.1, U1.17 (SCL); also elsewhere on the board
/SCL_IMU: R3.2, TP14.1, U6.23 (SCL); also elsewhere on the board
/SDA_GPS: TP9.1, U1.16 (SDA); also elsewhere on the board
/SDA_IMU: R2.2, TP6.1, U6.24 (SDA); also elsewhere on the board
GND: C1.1, C22.2, C23.1, C24.2, C25.1, C26.1, J3.2 (Ext), U1.1 (GND), U1.10 (GND), U1.12 (GND), U6.1 (CLKIN), U6.9 (AD0), U6.11 (FSYNC), U6.18 (GND); also elsewhere on the board
unnamed: C22.1, L2.1, R11.2
unnamed: J3.1 (In), L1.2, U1.11 (RF_IN)
unnamed: L1.1, L2.2
unnamed: R11.1, U1.14 (VCC_RF)
unnamed: TP11.1, U1.9 (~RESET)
unnamed: TP12.1, U1.18 (~SAFEBOOT)
unnamed: C26.2, U6.20 (CPOUT)
unnamed: C25.2, U6.10 (REGOUT)

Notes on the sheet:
0x68
